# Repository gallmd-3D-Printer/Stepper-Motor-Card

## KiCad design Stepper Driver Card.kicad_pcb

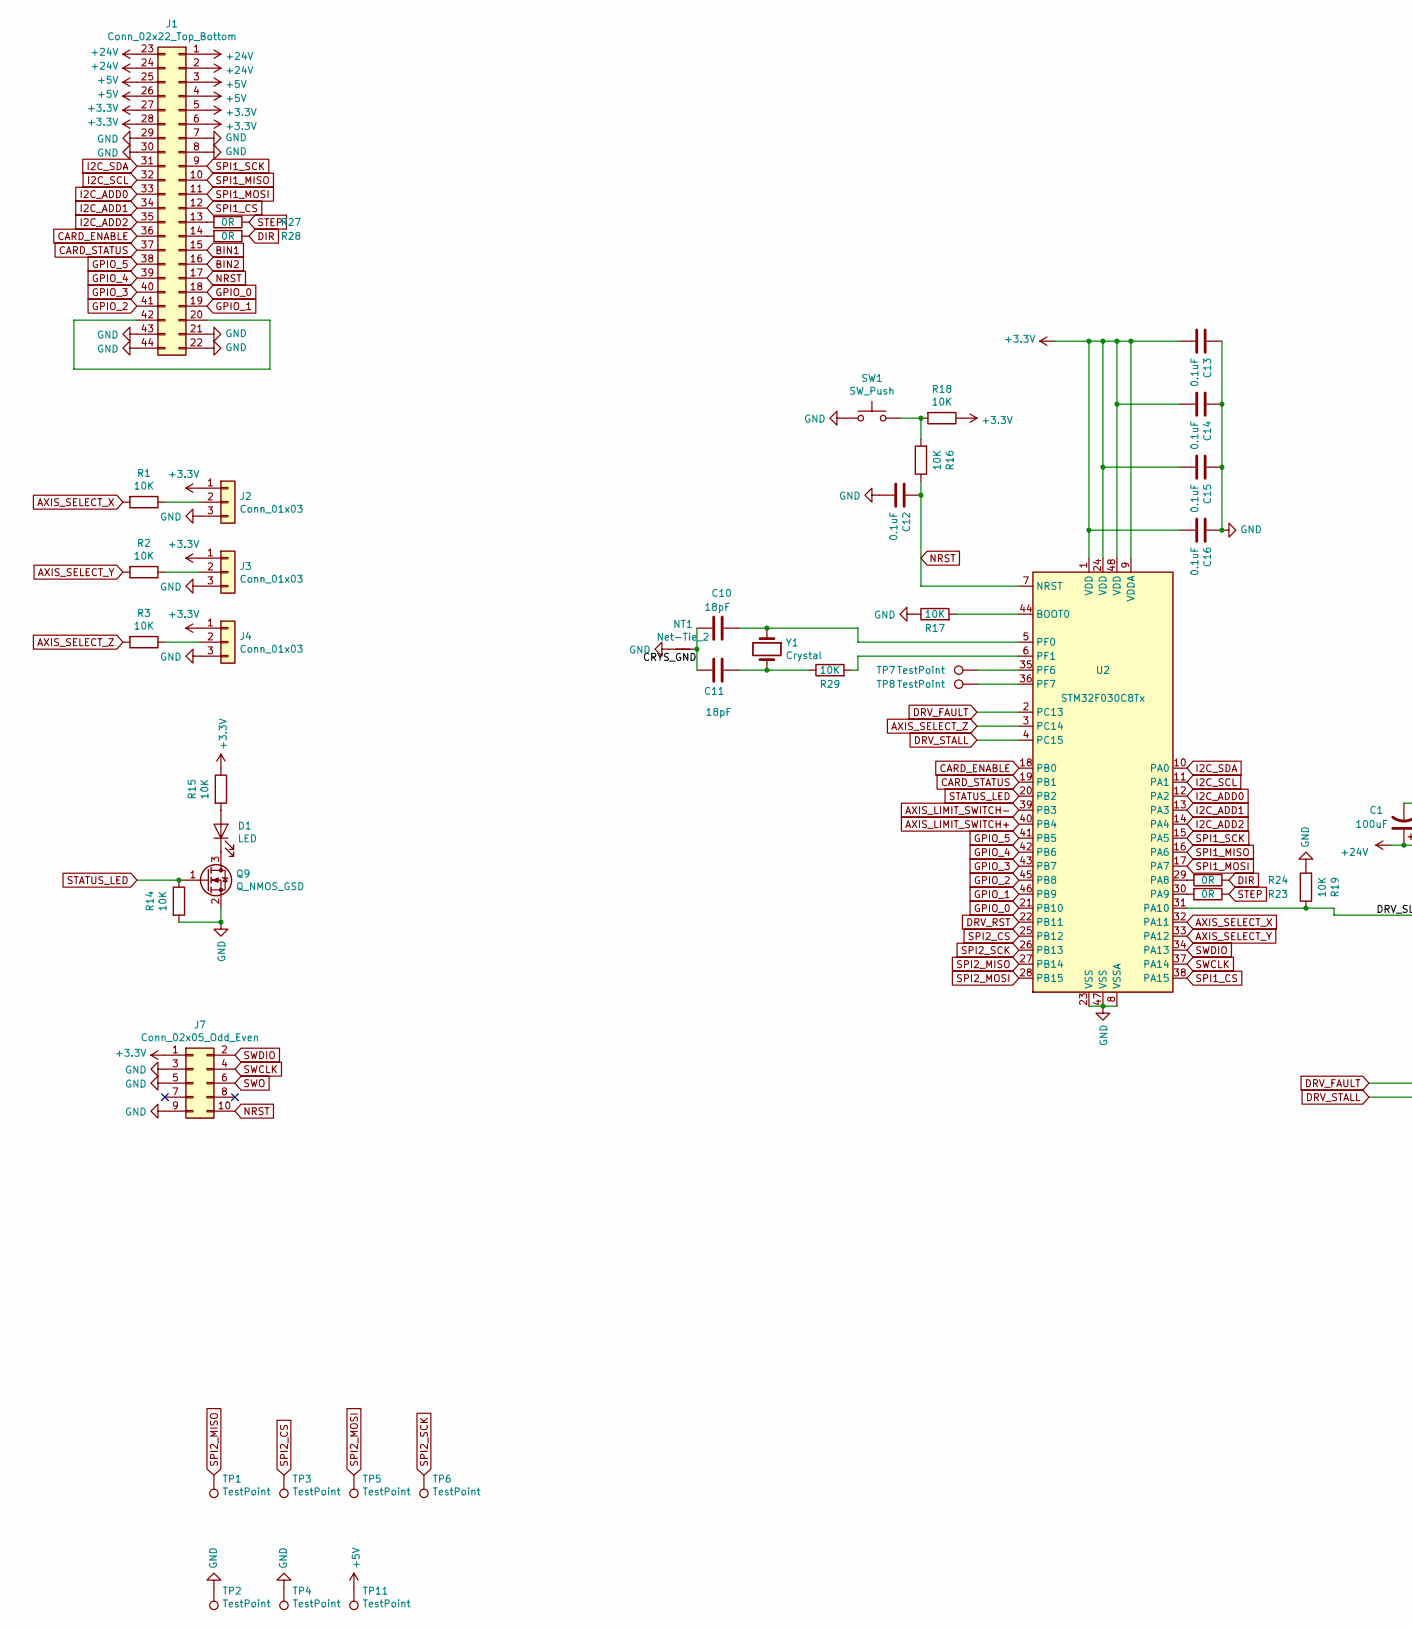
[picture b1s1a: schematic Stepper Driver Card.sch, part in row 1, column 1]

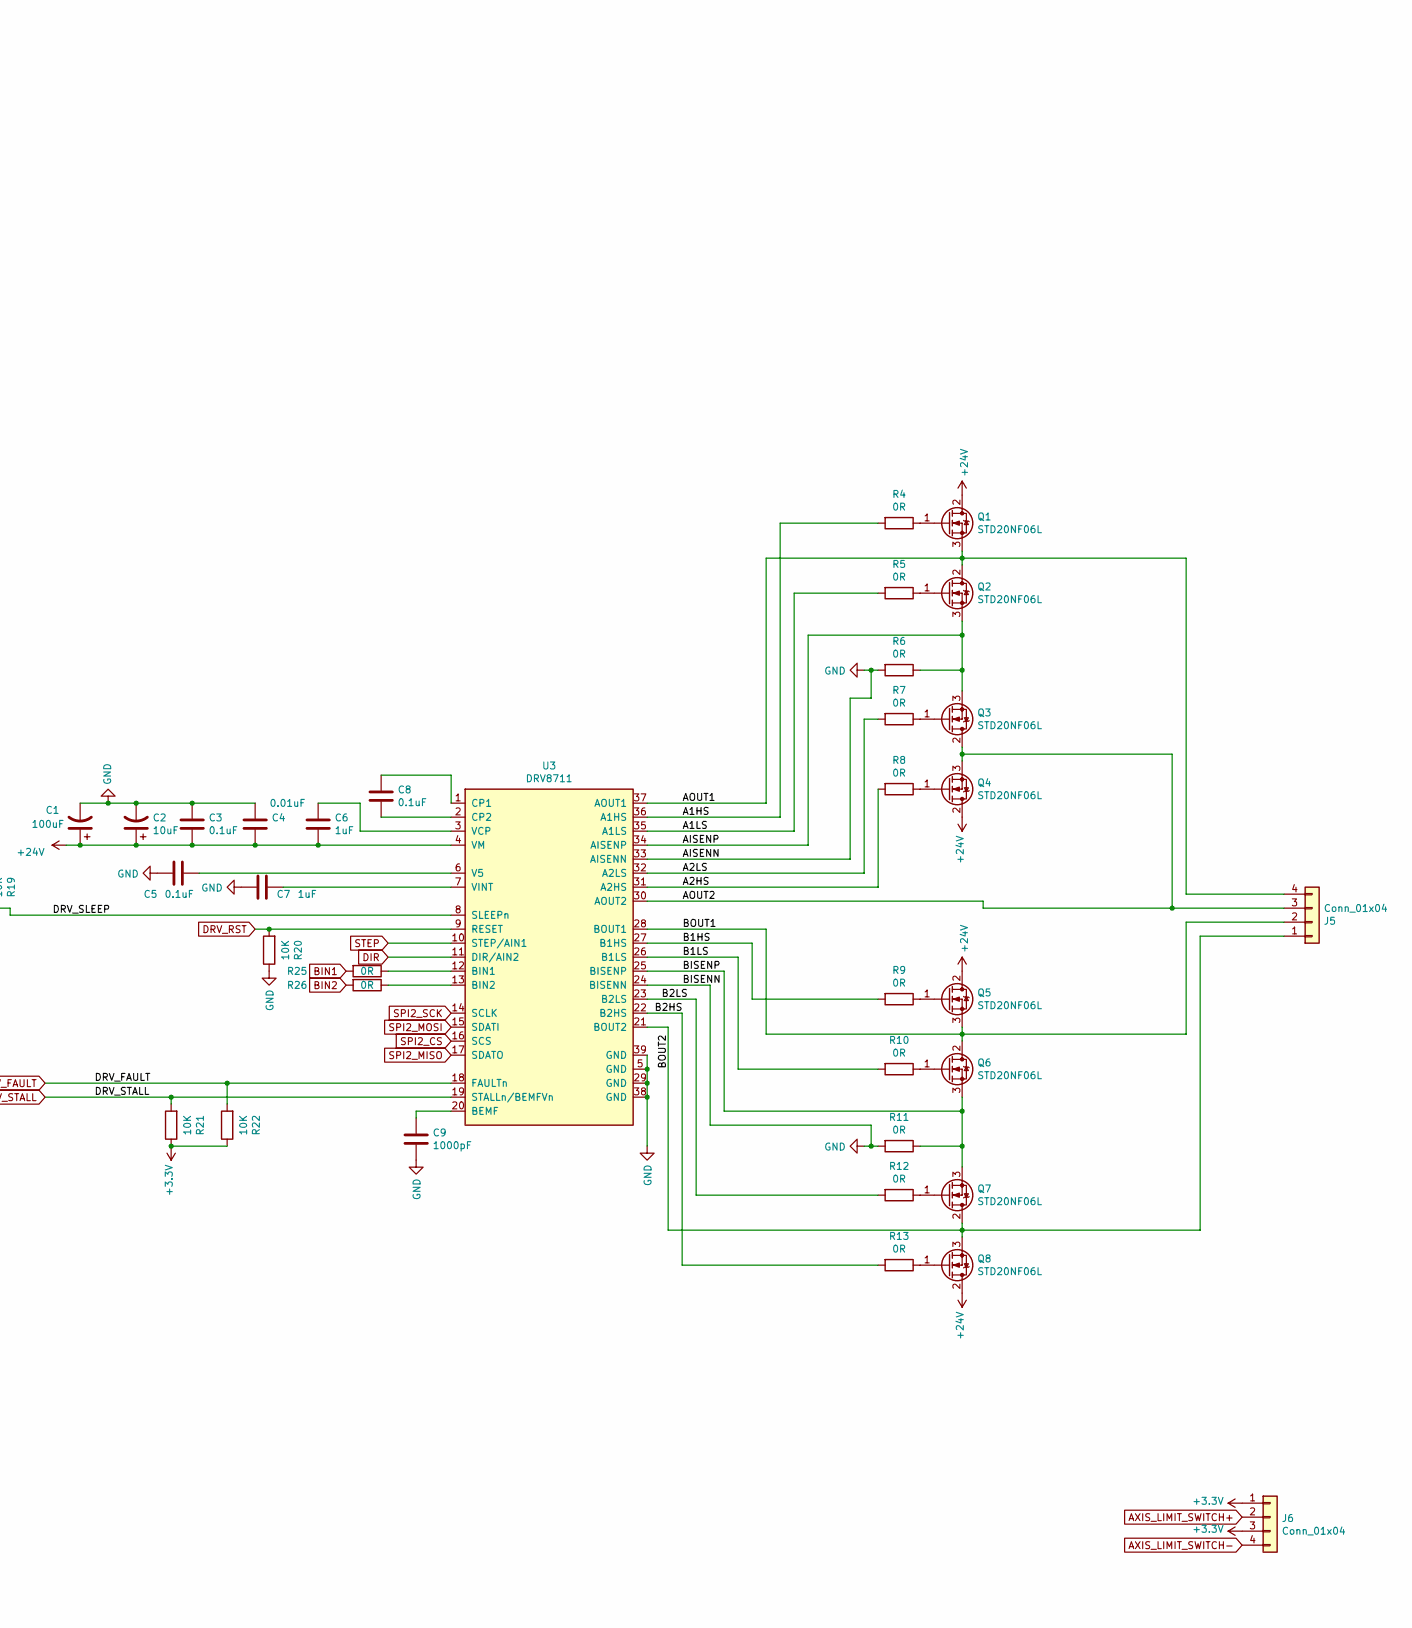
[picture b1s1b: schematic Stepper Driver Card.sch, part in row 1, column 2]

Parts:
C1: 100uF; CP_Radial_D8.0mm_P3.50mm
C2: 10uF; CP_Radial_D8.0mm_P3.50mm
C3, C5, C8, C12, C13, C14, C15, C16: 0.1uF; C_0603_1608Metric_Pad1.05x0.95mm_HandSolder
C4: 0.01uF; C_0603_1608Metric_Pad1.05x0.95mm_HandSolder
C6, C7: 1uF; C_0603_1608Metric_Pad1.05x0.95mm_HandSolder
C9: 1000pF; C_0603_1608Metric_Pad1.05x0.95mm_HandSolder
C10, C11: 18pF; C_0603_1608Metric_Pad1.05x0.95mm_HandSolder
D1: LED; LED_1206_3216Metric_Pad1.42x1.75mm_HandSolder
J1: Conn_02x22_Top_Bottom; CARD_EDGE_5530843-4-44PIN
J2, J3, J4: Conn_01x03; PinHeader_1x03_P2.54mm_Vertical
J5: Conn_01x04; PhoenixContact_MSTBA_2,5_4-G-5,08_1x04_P5.08mm_Horizontal
J6: Conn_01x04; PhoenixContact_MC_1,5_4-G-3.5_1x04_P3.50mm_Horizontal
J7: Conn_02x05_Odd_Even; PinHeader_2x05_P1.27mm_Vertical
NT1: Net-Tie_2; NetTie-2_SMD_Pad0.5mm
Q1, Q2, Q3, Q4, Q5, Q6, Q7, Q8: STD20NF06L; TO-252-2
Q9: Q_NMOS_GSD; SOT-323_SC-70_Handsoldering
R1, R2, R3, R14, R15, R16, R17, R18, R19, R20, R21, R22, R29: 10K; R_0603_1608Metric_Pad1.05x0.95mm_HandSolder
R4, R5, R7, R8, R9, R10, R12, R13, R23, R24, R25, R26, R27, R28: 0R; R_0603_1608Metric_Pad1.05x0.95mm_HandSolder
R6, R11: 0R; R_2512_6332Metric_Pad1.52x3.35mm_HandSolder
SW1: SW_Push; FSM2JMTR
TP1, TP2, TP3, TP4, TP5, TP6: TestPoint; TestPoint_Keystone_5015_Micro-Minature
TP7, TP8: TestPoint; PinHeader_1x01_P1.00mm_Vertical
TP11: TestPoint; Keystone_5010
U2: STM32F030C8Tx; LQFP-48_7x7mm_P0.5mm
U3: DRV8711; TSSOP-38-1_Power_Pad_4.4x9.7mm_P0.5mm
Y1: Crystal; Crystal_SMD_Abracon_ABM3-2Pin_5.0x3.2mm_HandSoldering; Part_Number ABM3-16.000MHZ-B2-T

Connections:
+3V3: C13.2, C14.2, C15.2, C16.2, J1.5, J1.6, J1.27, J1.28, J2.1, J3.1, J4.1, J6.1, J6.3, J7.1, R15.1, R18.1, R21.1, R22.1, U2.1 (VDD), U2.9 (VDDA), U2.24 (VDD), U2.48 (VDD)
+5V: J1.3, J1.4, J1.25, J1.26, TP11.1
+24V: C1.1, C2.1, C3.2, C4.2, C6.1, J1.1, J1.2, J1.23, J1.24, Q1.2 (D), Q4.2 (D), Q5.2 (D), Q8.2 (D), U3.4 (VM)
/A1HS: R4.2, U3.36 (A1HS)
/A1LS: R5.2, U3.35 (A1LS)
/A2HS: R8.2, U3.31 (A2HS)
/A2LS: R7.2, U3.32 (A2LS)
/AISENP: Q2.3 (S), Q3.3 (S), R6.1, U3.34 (AISENP)
/AOUT1: J5.4, Q1.3 (S), Q2.2 (D), U3.37 (AOUT1)
/AOUT2: J5.3, Q3.2 (D), Q4.3 (S), U3.30 (AOUT2)
/B1HS: R9.2, U3.27 (B1HS)
/B1LS: R10.2, U3.26 (B1LS)
/B2HS: R13.2, U3.22 (B2HS)
/B2LS: R12.2, U3.23 (B2LS)
/BISENP: Q6.3 (S), Q7.3 (S), R11.1, U3.25 (BISENP)
/BOUT1: J5.2, Q5.3 (S), Q6.2 (D), U3.28 (BOUT1)
/BOUT2: J5.1, Q7.2 (D), Q8.3 (S), U3.21 (BOUT2)
/CRYS_GND: C10.2, C11.1, NT1.2
/DRV_SLEEP: R19.1, U2.31 (PA10), U3.8 (SLEEPn)
AXIS_LIMIT_SWITCH+: J6.2, U2.40 (PB4)
AXIS_LIMIT_SWITCH-: J6.4, U2.39 (PB3)
AXIS_SELECT_X: R1.2, U2.32 (PA11)
AXIS_SELECT_Y: R2.2, U2.33 (PA12)
AXIS_SELECT_Z: R3.2, U2.3 (PC14)
BIN1: J1.15, R25.2
BIN2: J1.16, R26.2
CARD_ENABLE: J1.36, U2.18 (PB0)
CARD_STATUS: J1.37, U2.19 (PB1)
DIR: R24.1, R28.1, U3.11 (DIR/AIN2)
DRV_FAULT: R22.2, U2.2 (PC13), U3.18 (FAULTn)
DRV_RST: R20.2, U2.22 (PB11), U3.9 (RESET)
DRV_STALL: R21.2, U2.4 (PC15), U3.19 (STALLn/BEMFVn)
GND: C1.2, C2.2, C3.1, C4.1, C5.2, C7.2, C9.2, C12.2, C13.1, C14.1, C15.1, C16.1, J1.7, J1.8, J1.21, J1.22, J1.29, J1.30, J1.43, J1.44, J2.3, J3.3, J4.3, J7.3, J7.5, J7.9, NT1.1, Q9.2 (S), R6.2, R11.2, R14.2, R17.1, R19.2, R20.1, SW1.1, TP2.1, TP4.1, U2.8 (VSSA), U2.23 (VSS), U2.47 (VSS), U3.5 (GND), U3.24 (BISENN), U3.29 (GND), U3.33 (AISENN), U3.38 (GND), U3.39 (GND)
GPIO_0: J1.18, U2.21 (PB10)
GPIO_1: J1.19, U2.46 (PB9)
GPIO_2: J1.41, U2.45 (PB8)
GPIO_3: J1.40, U2.43 (PB7)
GPIO_4: J1.39, U2.42 (PB6)
GPIO_5: J1.38, U2.41 (PB5)
I2C_ADD0: J1.33, U2.12 (PA2)
I2C_ADD1: J1.34, U2.13 (PA3)
I2C_ADD2: J1.35, U2.14 (PA4)
I2C_SCL: J1.32, U2.11 (PA1)
I2C_SDA: J1.31, U2.10 (PA0)
NRST: C12.1, J1.17, J7.10, R16.1, U2.7 (NRST)
unnamed: C5.1, U3.6 (V5)
unnamed: C6.2, U3.3 (VCP)
unnamed: C7.1, U3.7 (VINT)
unnamed: C8.1, U3.1 (CP1)
unnamed: C8.2, U3.2 (CP2)
unnamed: C9.1, U3.20 (BEMF)
unnamed: C10.1, U2.5 (PF0), Y1.1
unnamed: C11.2, R29.1, Y1.2
unnamed: D1.1 (K), Q9.3 (D)
unnamed: D1.2 (A), R15.2
unnamed: J1.13, R27.2
unnamed: J1.14, R28.2
unnamed: J1.20, J1.42
unnamed: J2.2, R1.1
unnamed: J3.2, R2.1
unnamed: J4.2, R3.1
unnamed: Q1.1 (G), R4.1
unnamed: Q2.1 (G), R5.1
unnamed: Q3.1 (G), R7.1
unnamed: Q4.1 (G), R8.1
unnamed: Q5.1 (G), R9.1
unnamed: Q6.1 (G), R10.1
unnamed: Q7.1 (G), R12.1
unnamed: Q8.1 (G), R13.1
unnamed: R16.2, R18.2, SW1.2
unnamed: R17.2, U2.44 (BOOT0)
unnamed: R23.2, U2.30 (PA9)
unnamed: R24.2, U2.29 (PA8)
unnamed: R25.1, U3.12 (BIN1)
unnamed: R26.1, U3.13 (BIN2)
unnamed: R29.2, U2.6 (PF1)
unnamed: TP7.1, U2.35 (PF6)
unnamed: TP8.1, U2.36 (PF7)
SPI1_CS: J1.12, U2.38 (PA15)
SPI1_MISO: J1.10, U2.16 (PA6)
SPI1_MOSI: J1.11, U2.17 (PA7)
SPI1_SCK: J1.9, U2.15 (PA5)
SPI2_CS: TP3.1, U2.25 (PB12), U3.16 (SCS)
SPI2_MISO: TP1.1, U2.27 (PB14), U3.17 (SDATO)
SPI2_MOSI: TP5.1, U2.28 (PB15), U3.15 (SDATI)
SPI2_SCK: TP6.1, U2.26 (PB13), U3.14 (SCLK)
STATUS_LED: Q9.1 (G), R14.1, U2.20 (PB2)
STEP: R23.1, R27.1, U3.10 (STEP/AIN1)
SWCLK: J7.4, U2.37 (PA14)
SWDIO: J7.2, U2.34 (PA13)
SWO: J7.6

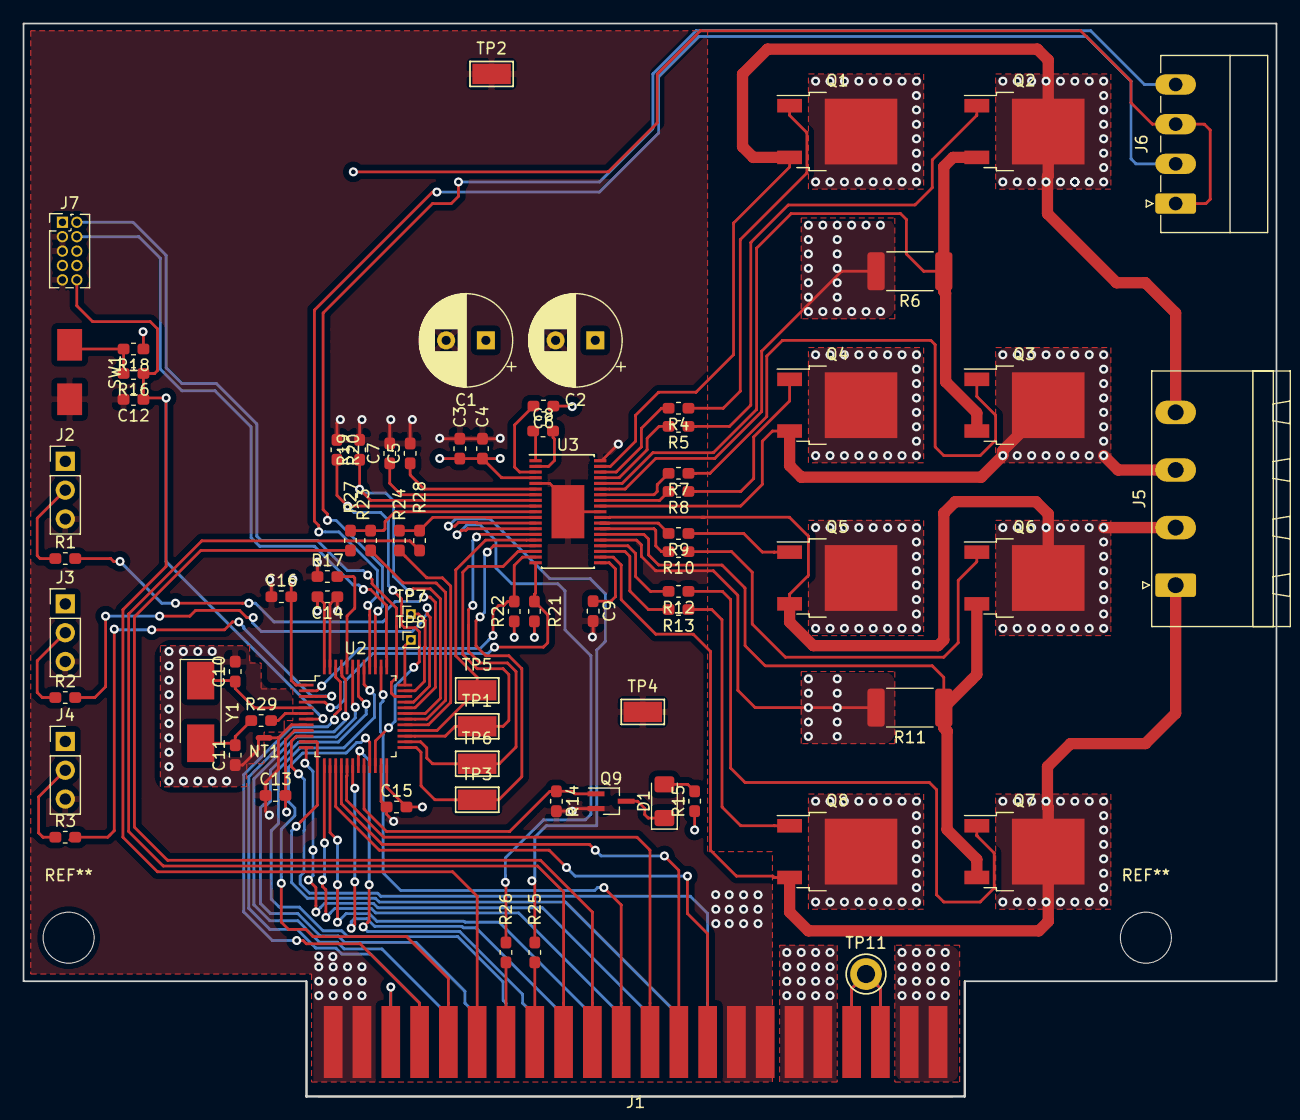
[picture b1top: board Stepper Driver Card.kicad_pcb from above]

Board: 4 copper layers, 110.5 x 94.6 mm, 76 parts (0 on the bottom side), 90 nets.

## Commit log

2019-12-10 worked on motor driver layout
2019-12-30 All traces connected, board needs to be cleaned up.
